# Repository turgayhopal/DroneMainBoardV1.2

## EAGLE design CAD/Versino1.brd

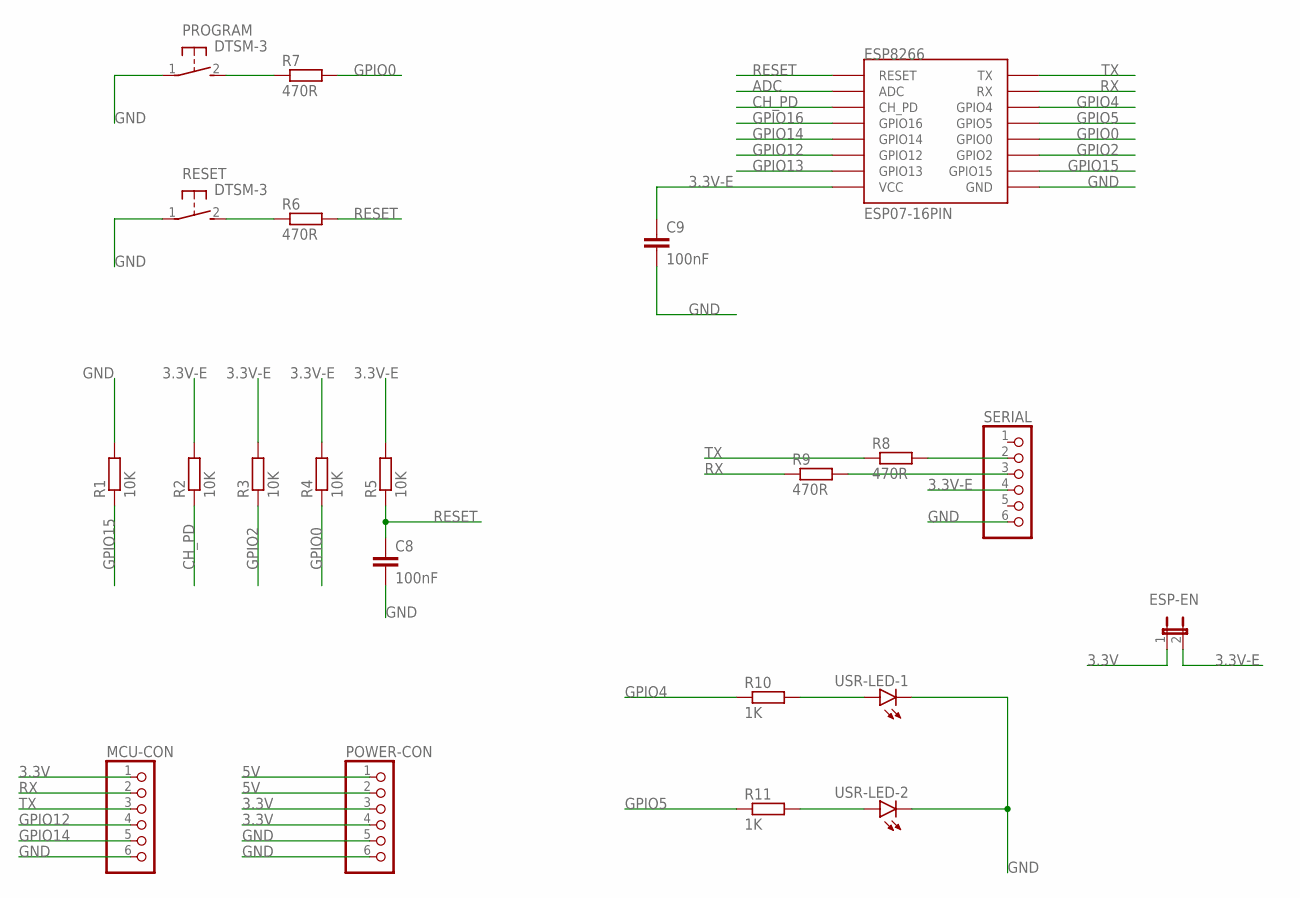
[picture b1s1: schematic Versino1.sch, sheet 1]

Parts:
C8, C9: 100nF; C0603
ESP8266: ESP07-16PIN
ESP-EN: JP1E; JP1
MCU-CON: PINHD-1X6; 1X06
POWER-CON: PINHD-1X6; 1X06
PROGRAM: DTSM-3
R1, R2, R3, R4, R5: 10K; R0603
R6, R7, R8, R9: 470R; R0603
R10, R11: 1K; R0603
RESET: DTSM-3
SERIAL: PINHD-1X6; 1X06
USR-LED-1, USR-LED-2: LEDCHIP-LED0805; CHIP-LED0805

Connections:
3.3V: ESP-EN.1, MCU-CON.1, POWER-CON.3, POWER-CON.4; also elsewhere on the board
3.3V-E: C9.1, ESP8266.VCC, ESP-EN.2, R2.2, R3.2, R4.2, R5.2, SERIAL.4
5V: POWER-CON.1, POWER-CON.2; also elsewhere on the board
ADC: ESP8266.ADC
CH_PD: ESP8266.CH_PD, R2.1
GND: C8.2, C9.2, ESP8266.GND, MCU-CON.6, POWER-CON.5, POWER-CON.6, PROGRAM.1, R1.2, RESET.1, SERIAL.6, USR-LED-1.C, USR-LED-2.C; also elsewhere on the board
GPIO0: ESP8266.GPIO0, R4.1, R7.2
GPIO2: ESP8266.GPIO2, R3.1
GPIO4: ESP8266.GPIO4, R10.1
GPIO5: ESP8266.GPIO5, R11.1
GPIO12: ESP8266.GPIO12, MCU-CON.4
GPIO13: ESP8266.GPIO13
GPIO14: ESP8266.GPIO14, MCU-CON.5
GPIO15: ESP8266.GPIO15, R1.1
GPIO16: ESP8266.GPIO16
unnamed: PROGRAM.2, R7.1
unnamed: R6.1, RESET.2
unnamed: R8.2, SERIAL.2
unnamed: R9.2, SERIAL.3
unnamed: R11.2, USR-LED-2.A
unnamed: R10.2, USR-LED-1.A
RESET: C8.1, ESP8266.REST (RESET), R5.1, R6.2
RX: ESP8266.RX, MCU-CON.2, R9.1
TX: ESP8266.TX, MCU-CON.3, R8.1

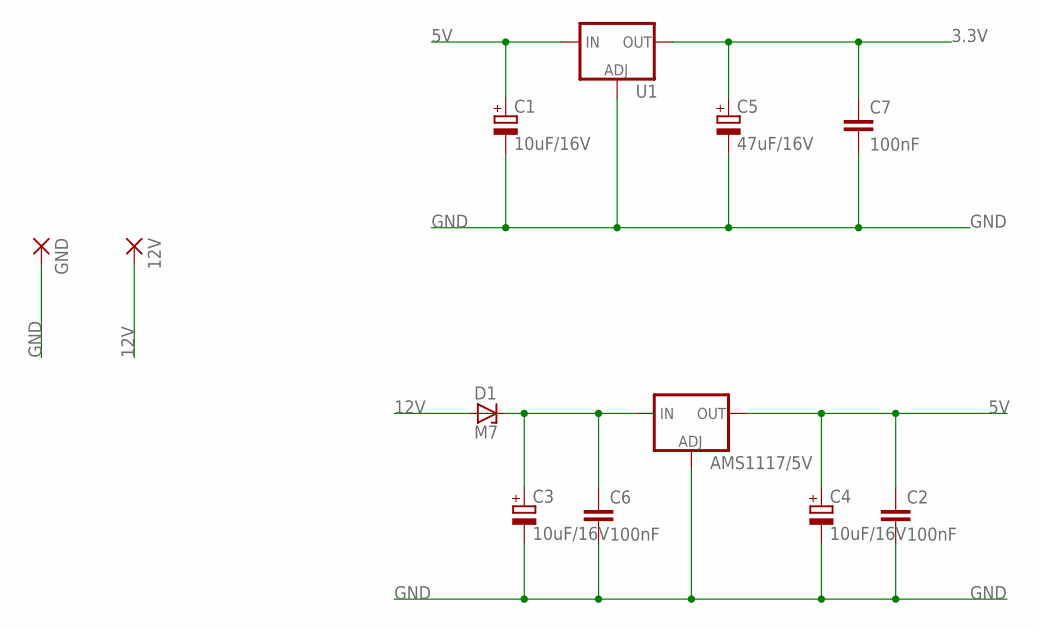
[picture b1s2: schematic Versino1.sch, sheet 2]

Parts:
12V: SMD5; SMD2,54-5,08
AMS1117/5V: V_REG_LM1117SOT223; SOT223
C1, C3, C4: 10uF/16V; SMC_B
C2, C6, C7: 100nF; C0603
C5: 47uF/16V; SMC_B
D1: M7; DO214AC
GND: SMD5; SMD2,54-5,08
U1: V_REG_LM1117SOT223; SOT223

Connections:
3.3V: C5.+, C7.1, U1.2 (OUT), U1.4 (OUT); also elsewhere on the board
5V: AMS1117/5V.2 (OUT), AMS1117/5V.4 (OUT), C1.+, C2.1, C4.+, U1.3 (IN); also elsewhere on the board
12V: 12V.1, D1.A
GND: AMS1117/5V.1 (ADJ), C1.-, C2.2, C3.-, C4.-, C5.-, C6.2, C7.2, GND.1, U1.1 (ADJ); also elsewhere on the board
unnamed: AMS1117/5V.3 (IN), C3.+, C6.1, D1.C

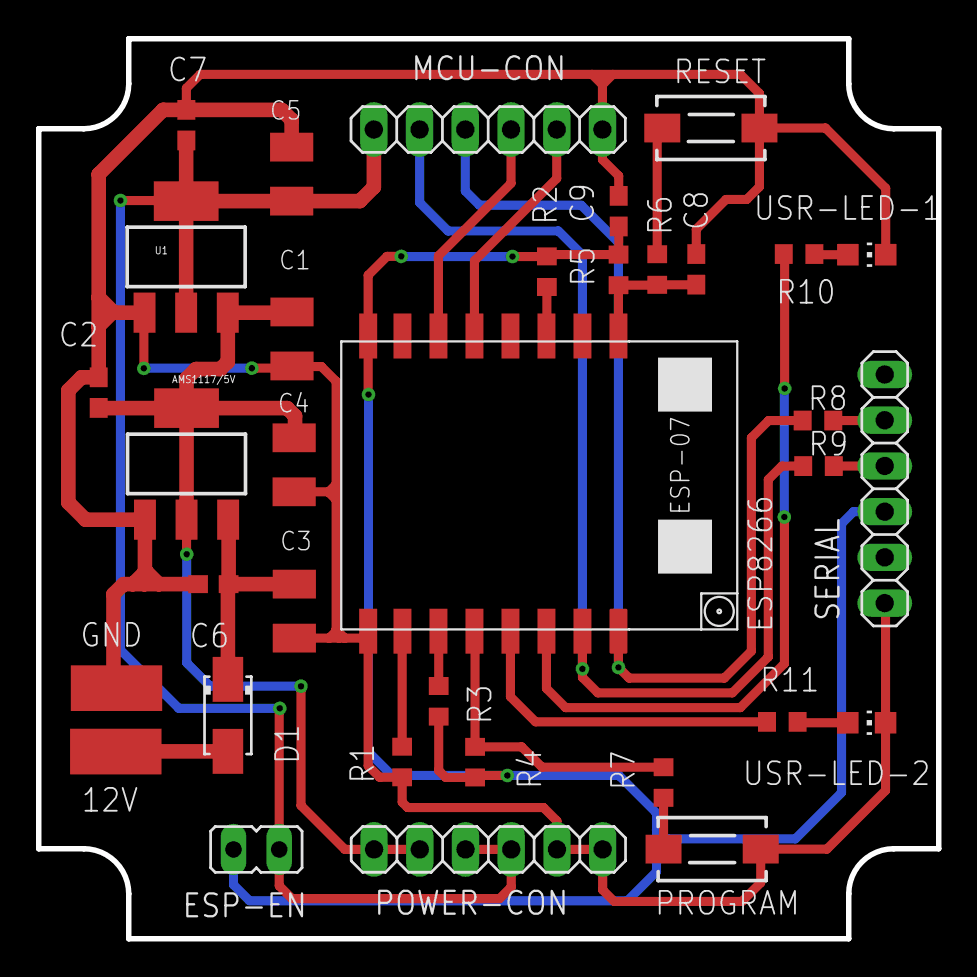
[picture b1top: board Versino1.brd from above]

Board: 2 copper layers, 50.0 x 50.0 mm, 34 parts (0 on the bottom side), 23 nets.

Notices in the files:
parts and their libraries:
SparkFun-IC-Power: Licensing: Creative Commons ShareAlike 4.0 International - https://creativecommons.org/licenses/by-sa/4.0
